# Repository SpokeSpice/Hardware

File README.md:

# Hardware design files for the SpokeSpice project

## Overview

The project is divided into two parts, the controller and the arms. Typically a system would have 4 arms, each running at an angle of 90 degrees to the next.

This repository contains the [KiCad](https://kicad.org) project files for the controller and the arm PCBs.

## Controller

The controller board is based on the ESP32 microcontroller and features a USB-C connector for programming. It features a battery holder for an 18650 Li-Ion cell, a 3.3V LDO regulator, an SD card slot and 4 connectors for the arms.

Several mounting holes in the PCB allow it to be mounted in a variety of different spoke configurations.

For the sake of simplicity, the controller board does not feature a battery charging circuit. The battery must be charged externally.

There is also no voltage regulation for the LEDs. The LEDs are powered directly from the battery, which is a 3.7V cell. Consequently, there is also no reverse polarity protection to avoid the voltage drop and hence the energy loss. The battery must hence be inserted with the correct polarity.

## Arm

Arms are made to be attached to the spokes of a 28-inch bicycle wheel.

Several mounting holes in the PCB allow them to be mounted in a variety of different spoke configurations.

Each arm PCB features 32 WS2812B RGB LEDs and is connected to the controller board via a 4-pin cable. A second 4-pin cable can be used to daisy-chain a second arm on the other side of the wheel, which will then display the same content.

A hall effect sensor is used to detect the speed of the wheel and to synchronize the display with the rotation. There are two positions for this sensor.

## Additional hardware needed for the project

As the controller and the arms are mounted to the spokes with cable ties, it's recommended to install everything on a spare wheel that you mount and dismount from the bicycle as needed.

Several additional components are needed to build the project:

- At least one 18650 Li-Ion cell, and a charger
- 4-pin JST PH 2.0mm pitch cables to connect the arms to the controller. The length of the cables will depend on the size of the wheel and the position of the controller, but for a 4 arm setup you should typically get away with the following items:
  - 2x [connector housing PHR-4](https://octopart.com/phr-4-jst-279167?r=sp) per arm
  - 4x [4" cables](https://octopart.com/asphsph24k102-jst-99062288) for 2 arms
  - 4x [8" cables](https://octopart.com/asphsph24k152-jst-99062289) for 2 arms
- A lot of cable ties with 2-3 mm width
- For debugging and development, it was very useful to have a magnectic USB-C adapter, such as [this one](https://www.amazon.com/aucon-Magnetic-Connector-Charging-Transfer/dp/B098J4R2D8/). You will have to stop the wheel very often to test and tweak the setup, and the adapter allows you to quickly connect the controller to a computer without too much cable fiddling.

## Contributing

If you would like to contribute to the project, please open an issue or a pull request.

## License

This project is licensed under the CERN Open Hardware License v2. You may redistribute and modify this project under the terms of the CERN-OHL-S v2 (https://ohwr.org/cern_ohl_s_v2.txt). This documentation is distributed without any warranty. Without even the implied warranty of merchantability or fitness for a particular purpose.

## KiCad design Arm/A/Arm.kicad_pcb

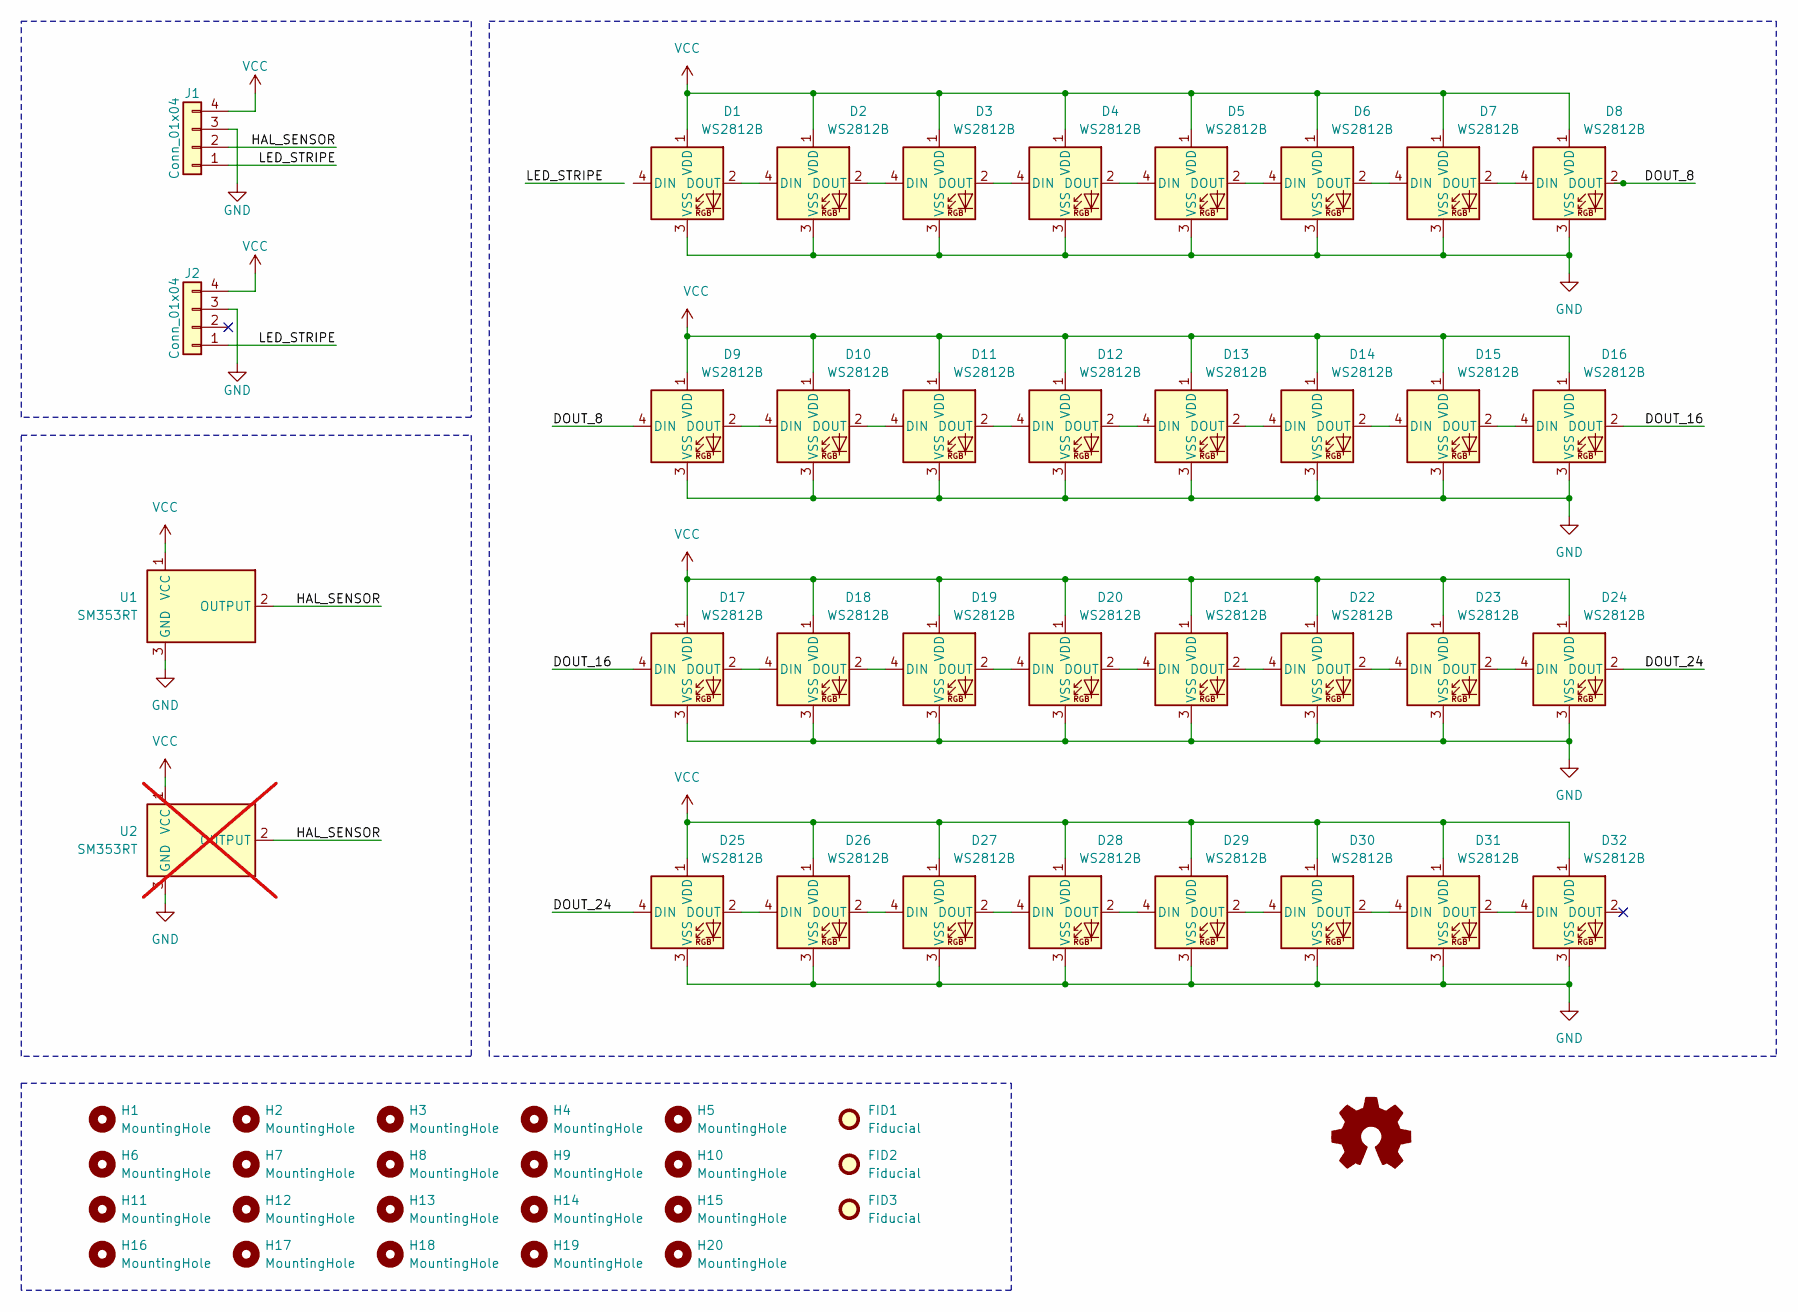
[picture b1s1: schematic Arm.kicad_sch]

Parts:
D1, D2, D3, D4, D5, D6, D7, D8, D9, D10, D11, D12, D13, D14, D15, D16, D17, D18, D19, D20, D21, D22, D23, D24, D25, D26, D27, D28, D29, D30, D31, D32: WS2812B; LED_WS2812B_PLCC4_5.0x5.0mm_P3.2mm; LCSC C2761795
FID1, FID2, FID3: Fiducial; Fiducial_0.5mm_Mask1mm
H1, H2, H3, H4, H5, H6, H7, H8, H9, H10, H11, H12, H13, H14, H15, H16, H17, H18, H19, H20: MountingHole; MountingHole_3.2mm_M3
J1, J2: Conn_01x04; JST_PH_S4B-PH-SM4-TB_1x04-1MP_P2.00mm_Horizontal; LCSC C265102
U1: SM353RT; SOT-23; LCSC C557249
U2: SM353RT; SOT-23; LCSC C557249; not fitted

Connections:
/DOUT_8: D8.2 (DOUT), D9.4 (DIN)
/DOUT_16: D16.2 (DOUT), D17.4 (DIN)
/DOUT_24: D24.2 (DOUT), D25.4 (DIN)
/HAL_SENSOR: J1.2, U1.2 (OUTPUT), U2.2 (OUTPUT)
/LED_STRIPE: D1.4 (DIN), J1.1, J2.1
GND: D1.3 (VSS), D2.3 (VSS), D3.3 (VSS), D4.3 (VSS), D5.3 (VSS), D6.3 (VSS), D7.3 (VSS), D8.3 (VSS), D9.3 (VSS), D10.3 (VSS), D11.3 (VSS), D12.3 (VSS), D13.3 (VSS), D14.3 (VSS), D15.3 (VSS), D16.3 (VSS), D17.3 (VSS), D18.3 (VSS), D19.3 (VSS), D20.3 (VSS), D21.3 (VSS), D22.3 (VSS), D23.3 (VSS), D24.3 (VSS), D25.3 (VSS), D26.3 (VSS), D27.3 (VSS), D28.3 (VSS), D29.3 (VSS), D30.3 (VSS), D31.3 (VSS), D32.3 (VSS), J1.3, J2.3, U1.3 (GND), U2.3 (GND)
unnamed: D1.2 (DOUT), D2.4 (DIN)
unnamed: D2.2 (DOUT), D3.4 (DIN)
unnamed: D3.2 (DOUT), D4.4 (DIN)
unnamed: D4.2 (DOUT), D5.4 (DIN)
unnamed: D5.2 (DOUT), D6.4 (DIN)
unnamed: D6.2 (DOUT), D7.4 (DIN)
unnamed: D7.2 (DOUT), D8.4 (DIN)
unnamed: D9.2 (DOUT), D10.4 (DIN)
unnamed: D10.2 (DOUT), D11.4 (DIN)
unnamed: D11.2 (DOUT), D12.4 (DIN)
unnamed: D12.2 (DOUT), D13.4 (DIN)
unnamed: D13.2 (DOUT), D14.4 (DIN)
unnamed: D14.2 (DOUT), D15.4 (DIN)
unnamed: D15.2 (DOUT), D16.4 (DIN)
unnamed: D17.2 (DOUT), D18.4 (DIN)
unnamed: D18.2 (DOUT), D19.4 (DIN)
unnamed: D19.2 (DOUT), D20.4 (DIN)
unnamed: D20.2 (DOUT), D21.4 (DIN)
unnamed: D21.2 (DOUT), D22.4 (DIN)
unnamed: D22.2 (DOUT), D23.4 (DIN)
unnamed: D23.2 (DOUT), D24.4 (DIN)
unnamed: D25.2 (DOUT), D26.4 (DIN)
unnamed: D26.2 (DOUT), D27.4 (DIN)
unnamed: D27.2 (DOUT), D28.4 (DIN)
unnamed: D28.2 (DOUT), D29.4 (DIN)
unnamed: D29.2 (DOUT), D30.4 (DIN)
unnamed: D30.2 (DOUT), D31.4 (DIN)
unnamed: D31.2 (DOUT), D32.4 (DIN)
VCC: D1.1 (VDD), D2.1 (VDD), D3.1 (VDD), D4.1 (VDD), D5.1 (VDD), D6.1 (VDD), D7.1 (VDD), D8.1 (VDD), D9.1 (VDD), D10.1 (VDD), D11.1 (VDD), D12.1 (VDD), D13.1 (VDD), D14.1 (VDD), D15.1 (VDD), D16.1 (VDD), D17.1 (VDD), D18.1 (VDD), D19.1 (VDD), D20.1 (VDD), D21.1 (VDD), D22.1 (VDD), D23.1 (VDD), D24.1 (VDD), D25.1 (VDD), D26.1 (VDD), D27.1 (VDD), D28.1 (VDD), D29.1 (VDD), D30.1 (VDD), D31.1 (VDD), D32.1 (VDD), J1.4, J2.4, U1.1 (VCC), U2.1 (VCC)

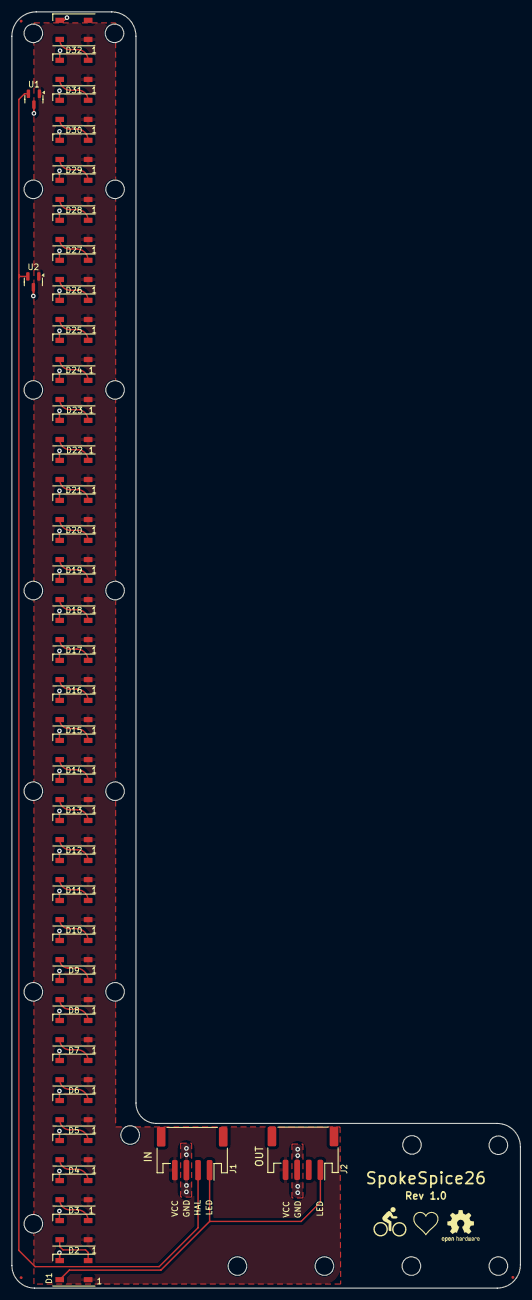
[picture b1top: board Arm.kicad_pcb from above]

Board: 2 copper layers, 87.7 x 220.1 mm, 59 parts (0 on the bottom side), 35 nets.

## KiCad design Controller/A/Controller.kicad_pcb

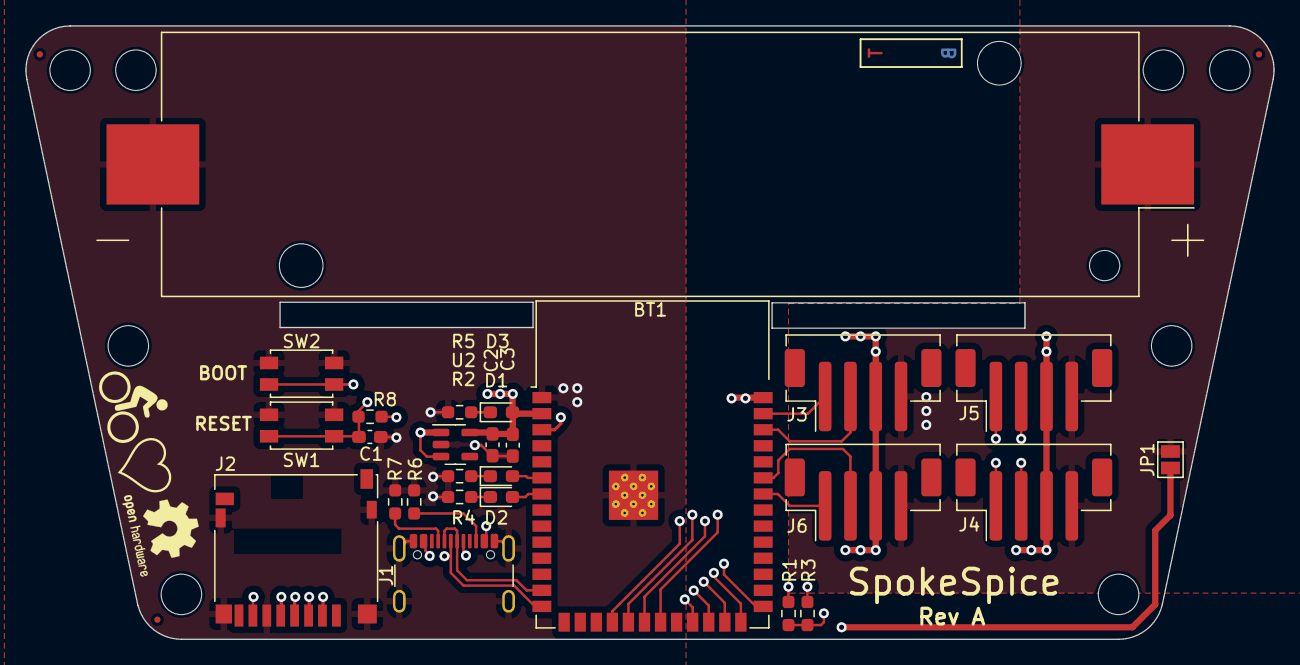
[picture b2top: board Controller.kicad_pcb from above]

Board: 4 copper layers, 98.7 x 48.5 mm, 37 parts (0 on the bottom side), 27 nets.

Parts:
BT1: Battery_Cell; BatteryHolder_Keystone_1042_1x18650
C1: 1uF; C_0603_1608Metric_Pad1.08x0.95mm_HandSolder
C2: 10uF; C_0603_1608Metric_Pad1.08x0.95mm_HandSolder
C3: 0.1uF; C_0603_1608Metric_Pad1.08x0.95mm_HandSolder
D1, D2, D3: LED 10 mA green; LED_0603_1608Metric_Pad1.05x0.95mm_HandSolder
FID1, FID2, FID3: Fiducial; Fiducial_0.5mm_Mask1mm
H1, H2, H3, H4, H5, H6, H7, H8: MountingHole; MountingHole_3.2mm_M3
J1: USB_C_Receptacle_USB2.0_14P; USB_C_Receptacle_GCT_USB4105-xx-A_16P_TopMnt_Horizontal
J2: Micro_SD_Card_Det; microSD_HC_Hirose_DM3D-SF
J3, J4, J5, J6: Conn_01x04; JST_PH_B4B-PH-SM4-TB_1x04-1MP_P2.00mm_Vertical
JP1: SolderJumper_2_Open; SolderJumper-2_P1.3mm_Open_Pad1.0x1.5mm
R1, R3, R8: 10k; R_0603_1608Metric_Pad0.98x0.95mm_HandSolder
R2, R4, R5: 1k; R_0603_1608Metric_Pad0.98x0.95mm_HandSolder
R6, R7: 5.1k; R_0603_1608Metric_Pad0.98x0.95mm_HandSolder
SW1, SW2: SW_Push; SW_SPST_EVQP2
U1: ESP32-S3-WROOM-1
U2: NCP163ASN330T1G; SOT-23-5

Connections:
+3V3: C2.1, C3.1, D3.2 (A), J2.4 (VDD), R1.1, R3.1, R8.1, U1.2 (3V3), U2.5 (VOUT)
/D+: J1.A6 (D+), J1.B6 (D+), U1.14 (IO20)
/D-: J1.A7 (D-), J1.B7 (D-), U1.13 (IO19)
/HAL_SENSOR_0: J3.2, U1.38 (IO2)
/HAL_SENSOR_1: J5.2, U1.19 (IO11)
/HAL_SENSOR_2: J4.2, U1.20 (IO12)
/HAL_SENSOR_3: J6.2, U1.35 (IO42)
/IO0: SW2.2, U1.27 (IO0)
/LED1: D2.2 (A), U1.7 (IO7)
/LED2: D1.2 (A), U1.6 (IO6)
/LED_STRIPE_0: J3.1, U1.39 (IO1)
/LED_STRIPE_1: J5.1, U1.18 (IO10)
/LED_STRIPE_2: J4.1, U1.21 (IO13)
/LED_STRIPE_3: J6.1, U1.34 (IO41)
/SD_CLK: J2.5 (CLK), U1.25 (IO48)
/SD_CS: J2.2 (DAT3/CD), R1.2, U1.23 (IO21)
/SD_MISO: J2.7 (DAT0), R3.2, U1.26 (IO45)
/SD_MOSI: J2.3 (CMD), U1.24 (IO47)
/~MCU_RESET: C1.1, R8.2, SW1.2, U1.3 (EN)
GND: BT1.2 (-), C1.2, C2.2, C3.2, J1.A1 (GND), J1.A12 (GND), J1.B1 (GND), J1.B12 (GND), J1.S1 (SHIELD), J2.6 (VSS), J2.11 (SHIELD), J3.3, J4.3, J5.3, J6.3, R2.2, R4.2, R5.2, R6.2, R7.2, SW1.1, SW2.1, U1.1 (GND), U1.40 (GND), U1.41 (GND), U2.2 (GND)
unnamed: D1.1 (K), R2.1
unnamed: D2.1 (K), R4.1
unnamed: D3.1 (K), R5.1
unnamed: J1.A5 (CC1), R7.1
unnamed: J1.B5 (CC2), R6.1
VBUS: J1.A4 (VBUS), J1.A9 (VBUS), J1.B4 (VBUS), J1.B9 (VBUS), JP1.1 (A)
VCC: BT1.1 (+), J3.4, J4.4, J5.4, J6.4, JP1.2 (B), U2.1 (VIN), U2.3 (EN)

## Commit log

2024-03-29 Controller: Annotate arm connectors
2024-06-23 adapt length to fit 26" wheels

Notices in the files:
README.md:
CERN OHL v2
